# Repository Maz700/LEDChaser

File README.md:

# LEDChaser
My first project is the LED Chaser board. It is a small project just to learn the basics of PCB design and learn soldering. I am following the Blinky guide for this project. I am making the PCB in the shape of an oar blade because I like rowing.

PCB:      $4.00
Shipping: $3.12

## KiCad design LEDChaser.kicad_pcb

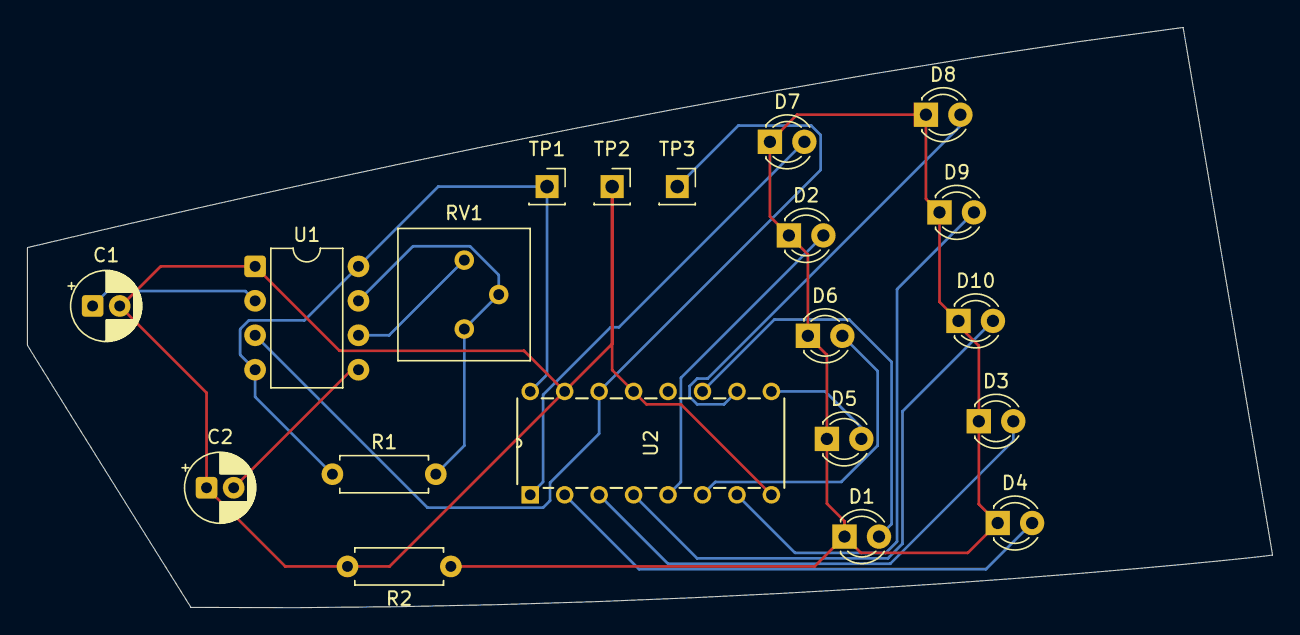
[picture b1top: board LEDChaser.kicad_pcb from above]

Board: 2 copper layers, 91.8 x 42.8 mm, 20 parts (0 on the bottom side), 18 nets.

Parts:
C1: 1 uF; CP_Radial_D5.0mm_P2.00mm
C2: 0.01 uF; CP_Radial_D5.0mm_P2.00mm
D1, D2, D3, D4, D5, D6, D7, D8, D9, D10: LED; LED_D3.0mm
R1: 1k; R_Axial_DIN0207_L6.3mm_D2.5mm_P7.62mm_Horizontal
R2: 470; R_Axial_DIN0207_L6.3mm_D2.5mm_P7.62mm_Horizontal
RV1: 50k; Potentiometer_Bourns_3386P_Vertical
TP1, TP2, TP3: TestPoint; PinSocket_1x01_P2.54mm_Vertical
U1: NE555P; DIP-8_W7.62mm
U2: 4017; N16

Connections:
+5V: R1.1, TP1.1, U1.4 (R), U1.8 (VCC), U2.16 (VDD)
GND: C1.2, C2.1, R2.2, TP2.1, U1.1 (GND), U2.8 (VSS), U2.13 (CKEN), U2.15 (Reset)
unnamed: D1.2 (A), U2.11 (Q9)
unnamed: D1.1 (K), D2.1 (K), D3.1 (K), D4.1 (K), D5.1 (K), D6.1 (K), D7.1 (K), D8.1 (K), D9.1 (K), D10.1 (K), R2.1
unnamed: D2.2 (A), U2.5 (Q6)
unnamed: D3.2 (A), U2.3 (Q0)
unnamed: D4.2 (A), U2.2 (Q1)
unnamed: D5.2 (A), U2.9 (Q8)
unnamed: D6.2 (A), U2.6 (Q7)
unnamed: D7.2 (A), U2.1 (Q5)
unnamed: D8.2 (A), U2.10 (Q4)
unnamed: D9.2 (A), U2.7 (Q3)
unnamed: D10.2 (A), U2.4 (Q2)
unnamed: C2.2, U1.5 (CV)
unnamed: R1.2, RV1.1, RV1.2, U1.7 (DIS)
unnamed: RV1.3, U1.6 (THR)
OUT: TP3.1, U1.3 (Q), U2.14 (CLK)
TR: C1.1, U1.2 (TR)

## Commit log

2025-12-27 Create PCB
